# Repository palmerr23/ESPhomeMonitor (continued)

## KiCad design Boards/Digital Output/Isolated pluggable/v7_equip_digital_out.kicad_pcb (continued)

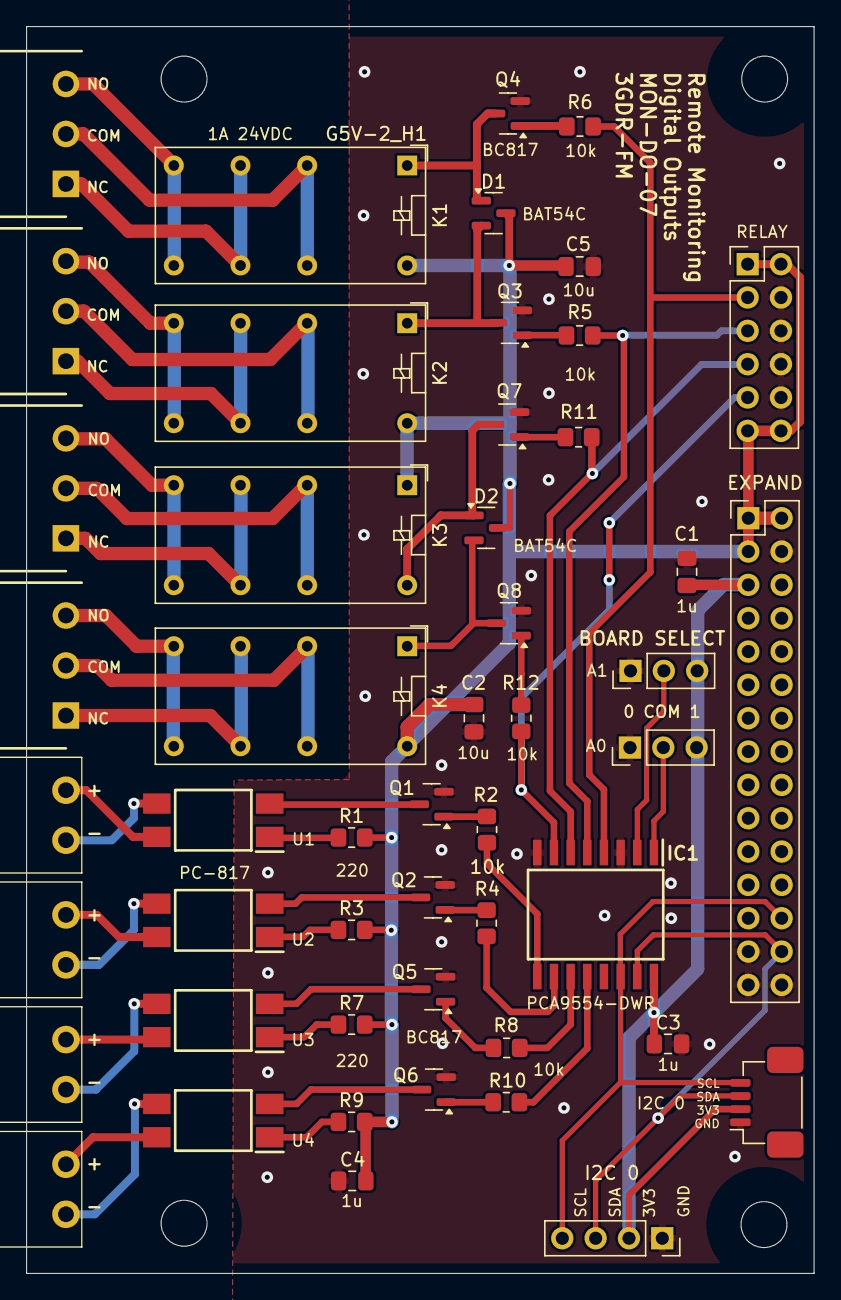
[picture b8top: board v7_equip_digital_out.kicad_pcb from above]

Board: 2 copper layers, 60.0 x 95.0 mm, 54 parts (0 on the bottom side), 55 nets.

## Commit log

2025-11-26 New files
2025-11-26 update files
2025-11-26 gallery
